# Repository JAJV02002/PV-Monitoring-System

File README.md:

# ☀️ PV Monitoring System

A photovoltaic monitoring project combining an ESP32 measurement unit, a PHP/MySQL web application, PCB designs and a printable enclosure. Developed for a bachelor’s thesis, the repository brings together the hardware and software resources for studying and recreating the system.

## 🌟 Features

- **Electrical measurements:** RMS voltage, RMS current, apparent power and an accumulated energy estimate.
- **Wi-Fi telemetry:** ESP32 measurements sent to the web application using HTTPS form requests.
- **Web dashboard:** Spanish and English interfaces with charts and historical readings.
- **Device management:** Devices grouped into matrices and measurement points.
- **Hardware resources:** KiCad schematic, board layout, required custom libraries, manufacturing outputs and a PCB assembly model.
- **Printable enclosure:** Separate STL files for the base and lid.

## 📁 Repository Structure

```text
PV-Monitoring-System/
├── hardware/
│   ├── bom/
│   │   └── EMON_BOM.xlsx
│   ├── cad/
│   │   ├── enclosure-base.stl
│   │   └── enclosure-lid.stl
│   └── pcb/
│       ├── kicad/
│       │   ├── monitoring-board.kicad_pro
│       │   ├── monitoring-board.kicad_sch
│       │   └── monitoring-board.kicad_pcb
│       ├── gerber/pcb-manufacturing.zip
│       └── 3d/pcb-assembly.zip
├── software/
│   ├── firmware/
│   │   ├── src/main.cpp
│   │   ├── include/secrets.example.h
│   │   └── platformio.ini
│   └── webapp/
│       ├── app/
│       ├── resources/
│       ├── index.php
│       └── .env.example
└── docs/
    └── architecture.md
```

Each component directory includes its own README with configuration and usage instructions.

## 🚀 Quick Start

### 1. Prepare the Hardware

1. Review the [Excel bill of materials](hardware/bom/EMON_BOM.xlsx).
2. Open the [KiCad project](hardware/pcb/kicad/README.md) and inspect the circuit and board layout.
3. Review the [manufacturing files](hardware/pcb/gerber/README.md) before ordering a PCB.
4. Inspect and print the [enclosure base and lid](hardware/cad/README.md), checking scale and fit against the board.

### 2. Configure the Web Application

Set up Apache, PHP with `mysqli`, and MySQL. Follow the [web application guide](software/webapp/README.md) to configure the document root, HTTPS and database connection.

```sh
cd software/webapp
cp .env.example .env
```

Enter the database credentials and a random hexadecimal device key in `.env`. A compatible database schema is required; the standalone schema is not yet published. See [database requirements](software/webapp/database/README.md).

### 3. Configure and Upload the Firmware

```sh
cd software/firmware
cp include/secrets.example.h include/secrets.h
```

Set the Wi-Fi credentials, HTTPS endpoint and matching device key in `secrets.h`, then build and upload:

```sh
pio run
pio run --target upload
pio device monitor
```

### 4. Connect the Measurement Point

Register the device with the web application, associate it with a measurement point, and confirm that readings appear in the database and dashboard. Check calibration against a suitable reference instrument.

## 📊 System Architecture

```text
Voltage and current signals
            │
            ▼
      ESP32 + sensors
  Sampling · RMS · Calibration
            │
            │ Wi-Fi / HTTPS form POST
            ▼
      PHP web application
    Controllers · Models · Views
            │
            ├── MySQL measurement storage
            │
            ▼
       Web dashboard
   Live views · History · Charts
```

## 🔧 Hardware

The Excel BOM contains core components and a high-precision sensing configuration, including the ESP32-DEVKITC-32E, HCPL-7800A-300E, OP177GSZ and HXS20-NP. Use the workbook as the component list and check compatibility with the intended PCB revision before assembly.

The manufacturing job describes a **two-layer, 1.6 mm board**, approximately **100.4 × 70.4 mm**. The enclosure is available as STL meshes, and the PCB assembly is available as a STEP model.

## 💻 Software Stack

| Component | Technology |
| --- | --- |
| Firmware | C++ / Arduino framework / PlatformIO |
| Microcontroller target | ESP32 development board (`esp32dev`) |
| Backend | PHP with an MVC-style structure |
| Database | MySQL through `mysqli` |
| Web server | Apache |
| Frontend | PHP views, HTML, CSS and JavaScript |
| Interface libraries | Bootstrap, Chart.js, jQuery and Popper |
| Telemetry | HTTPS with URL-encoded form fields |

## 📈 Measurement Details

- **ADC inputs:** GPIO 34 for voltage and GPIO 35 for current.
- **Sampling:** 12-bit resolution, 1,000 samples per block.
- **Averaging:** Voltage and current averaged over five blocks.
- **Power:** Apparent power calculated as `Vrms × Irms`.
- **Energy:** Time-integrated estimate assuming unity power factor; resets at restart.

The offset filter removes the DC component. Calibration and supported electrical ranges must be verified for the measurement hardware. See the [firmware guide](software/firmware/README.md) for timing and power-averaging details.

## 📖 Documentation

- [Hardware guide](hardware/README.md)
- [Bill of materials](hardware/bom/README.md)
- [Firmware setup](software/firmware/README.md)
- [Web application setup](software/webapp/README.md)
- [Database requirements](software/webapp/database/README.md)
- [Architecture and telemetry](docs/architecture.md)

## 📝 License
This project is licensed under the Creative Commons Attribution 4.0 License - see the [LICENSE](LICENSE.txt) file for details.

The web application is distributed under its existing [GNU GPL version 3 license](software/webapp/LICENSE). Third-party libraries retain their own notices. Separate licensing terms for the hardware, firmware and documentation are not yet specified.

## 🤝 Contributing

Improvements to documentation, reproducibility, hardware integration and software testing are welcome. Use repository issues to describe a problem or propose a change, and include the board revision and relevant configuration when reporting results.

## 🎓 Educational Use

The project supports study of embedded acquisition, electrical measurement, wireless telemetry and web-based monitoring in renewable-energy research.

## 🙏 Acknowledgments

- ESP32 and Arduino communities
- KiCad development community
- Bootstrap, Chart.js and other third-party library contributors

---

**Made with ❤️ for renewable energy monitoring**

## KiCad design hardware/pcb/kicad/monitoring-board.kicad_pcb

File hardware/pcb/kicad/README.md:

# 🛠️ KiCad PCB Design

Editable schematic, board layout and project-local component libraries for the monitoring unit.

## 📁 Project Files

- [monitoring-board.kicad_pro](monitoring-board.kicad_pro): project settings.
- [monitoring-board.kicad_sch](monitoring-board.kicad_sch): circuit schematic.
- [monitoring-board.kicad_pcb](monitoring-board.kicad_pcb): board layout.
- [fp-lib-table](fp-lib-table): project footprint-library registration.
- [sym-lib-table](sym-lib-table): project symbol-library registration.

## 🧩 Component Libraries

| Directory | Contents |
| --- | --- |
| [footprints.pretty](footprints.pretty) | 19 custom footprints, including the two logos placed on the board |
| [symbols](symbols) | 7 custom symbol libraries referenced by the schematic |
| [3dmodels](3dmodels) | 16 component STEP models referenced by the board |

The component selection follows the PCB component references and its design BOM, with the two board-logo footprints included because they are part of the layout. Unused parts, plugins, caches and backups are excluded. The purchasing BOM is [EMON_BOM.xlsx](../../bom/EMON_BOM.xlsx).

## 🚀 Getting Started

1. Install KiCad 8.0 or a compatible newer version with its standard symbol, footprint and 3D-model libraries.
2. Open `monitoring-board.kicad_pro` from this directory.
3. The project library tables resolve custom components through `${KIPRJMOD}`; no personal library-folder path is required.
4. Inspect the schematic, board and 3D view before editing or manufacturing.

Standard KiCad components remain linked to the installed libraries. The custom models in `3dmodels/` use project-relative paths. Keep this directory structure intact when copying the project.

## 🔗 Related Resources

- [Bill of materials](../../bom/README.md)
- [Manufacturing files](../gerber/README.md)
- [PCB assembly STEP model](../3d/README.md)
- [Enclosure meshes](../../cad/README.md)

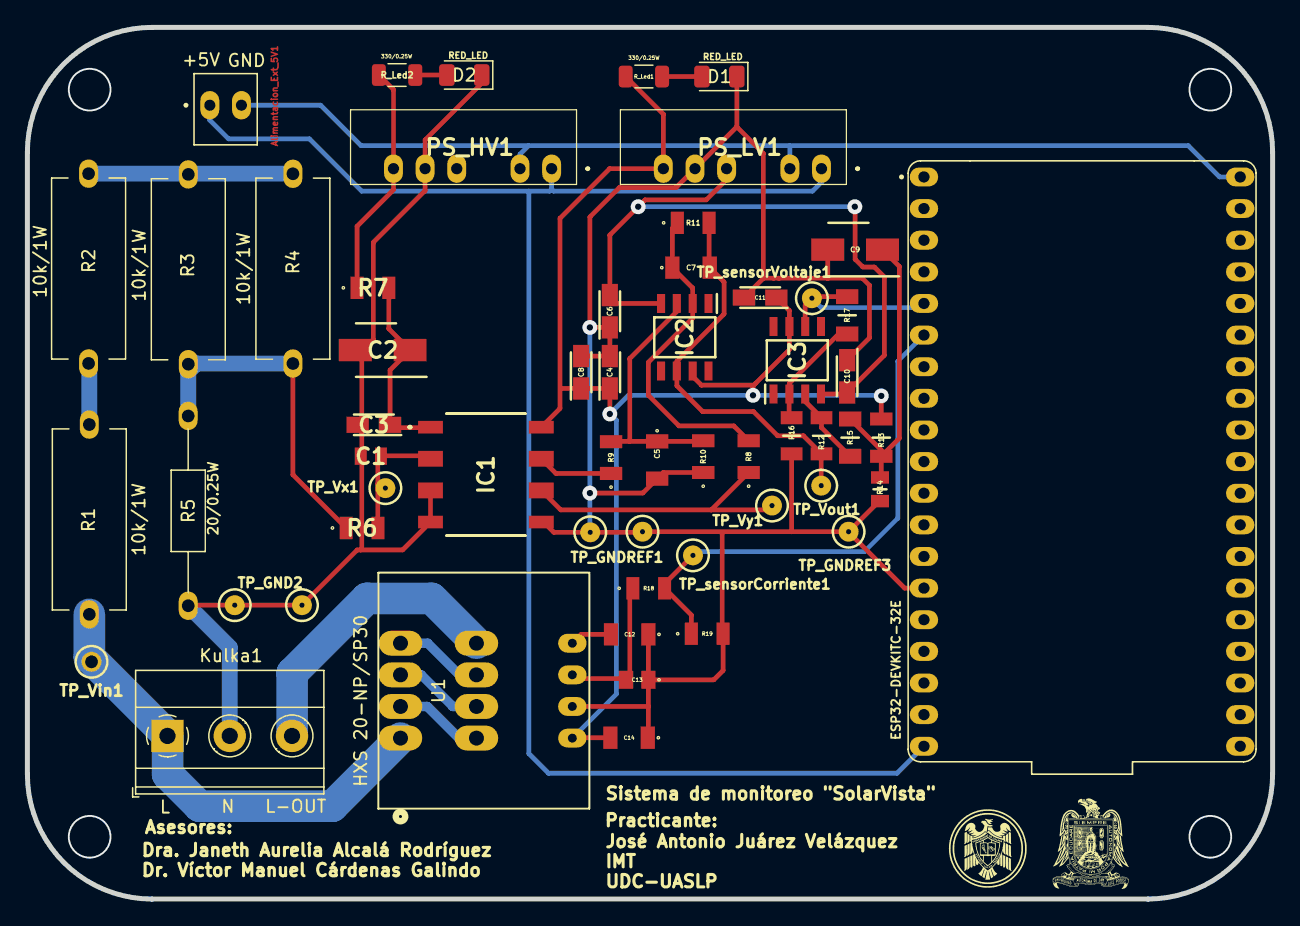
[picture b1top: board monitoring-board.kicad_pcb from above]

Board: 2 copper layers, 100.0 x 70.0 mm, 57 parts (0 on the bottom side), 31 nets.

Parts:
Alimentacion_Ext_5V1: 640456-2; header-640456-2
C1: 1000pF/Cer; capacitor-885012207060
C2, C9: 10uF/Elec; capacitor-EXV106M025A9BAA
C3, C4, C6, C8, C10, C11: 0.1uF/Tan; capacitor-TAJS104K020RNJ
C5, C7: 200pF/Cer; capacitor-C1206C201F4HACTU
C12, C14: 33nF/Cer; capacitor-C1206C201F4HACTU
C13: 3.3nF/Cer; capacitor-C0805C332F5GECAUTO7210
D1, D2: RED_LED; LED_1206_3216Metric
IC1: HCPL-7800A-300E
IC2, IC3: OP27GSZ
Kulka1: Screw_Terminal_01x03; TerminalBlock_Phoenix_MKDS-1,5-3_1x03_P5.00mm_Horizontal
PS_HV1: RB-0505D
PS_LV1: RB-0505D
R1, R2, R3, R4: 10k/1W; R_Axial_DIN0614_L14.3mm_D5.7mm_P15.24mm_Horizontal
R5: 20/0.25W; R_Axial_DIN0207_L6.3mm_D2.5mm_P15.24mm_Horizontal
R6, R19: 1k/0.25W; resistor-RCC12061R00FKEA
R7: 1/0.25W; resistor-RCC12061R00FKEA
R8, R9: 39k/0.25W; resistor-RCC12061R00FKEA
R10, R11: 22k/0.25W; resistor-RCC12061R00FKEA
R12, R16: 82k/0.25W; resistor-CRGH1206J82K
R13: 10k/0.25W; resistor-CRCW120610K0FKEAC
R14: 3.3k/0.25W; resistor-CR0805-FX-3301ELF
R15, R17: 100k/0.25W; resistor-CR1206-FX-1003ELF
R18: 1.2k/0.25W; resistor-RCC12061R00FKEA
R_Led1, R_Led2: 330/0.25W; R_1206_3216Metric
TP_GND1, TP_GND2: 5001; test-point-5001
TP_GNDREF1, TP_GNDREF2, TP_GNDREF3: 5001; test-point-5001
TP_Vin1: 5001; test-point-5001
TP_Vout1: 5001; test-point-5001
TP_Vx1: 5001; test-point-5001
TP_Vy1: 5001; test-point-5001
TP_sensorCorriente1: 5001; test-point-5001
TP_sensorVoltaje1: 5001; test-point-5001
U1: HXS 20-NP/SP30; HXS20-NP-SP30
U2: ESP32-DEVKITC-32E

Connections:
+5V_ESP: Alimentacion_Ext_5V1.1, PS_HV1.1 (+VIN), PS_LV1.1 (+VIN), U2.J2_19 (EXT_5V)
/currentSensor_Signal: R18.2, R19.1, TP_sensorCorriente1.1, U2.J2_6 (IO35)
/voltageSensor_Signal: IC3.6 (OUT), R17.2, TP_sensorVoltaje1.1, U2.J2_5 (IO34)
GNDREF: C4.2, C5.2, C6.1, C8.2, C9.2, C10.1, C11.2, C12.1, C13.1, C14.1, D1.1 (K), IC1.5 (GND2), PS_LV1.5 (COM), R10.1, R14.2, R16.1, R19.2, TP_GNDREF1.1, TP_GNDREF2.1, TP_GNDREF3.1, U1.10 (GND), U2.J2_14 (GND_J2_14)
GND_ESP: Alimentacion_Ext_5V1.2, PS_HV1.2 (-VIN), PS_LV1.2 (-VIN), U2.J3_1 (GND_J3_1)
Linea: Kulka1.1, R1.1, TP_Vin1.1, U1.1 (IN)
Linea_out: Kulka1.3, U1.8 (OUT)
unnamed: C9.1, R13.2, R14.1, R15.1
unnamed: C13.2, R18.1, U1.11 (OUT)
unnamed: D1.2 (A), R_Led1.1
unnamed: D2.2 (A), R_Led2.1
unnamed: C2.1, C3.1, IC1.1 (VDD1), R7.2
unnamed: C1.1, IC1.2 (VIN+), R6.2, TP_Vx1.1
unnamed: IC1.7 (VOUT+), R9.1
unnamed: IC1.6 (VOUT-), R8.1, TP_Vy1.1
unnamed: C5.1, IC2.3 (+IN), R9.2, R10.2
unnamed: C7.1, IC2.2 (-IN), R8.2, R11.1
unnamed: C7.2, IC2.6 (OUT), R11.2, R12.1, TP_Vout1.1
unnamed: IC3.3 (+IN), R12.2, R15.2
unnamed: IC3.2 (-IN), R16.2, R17.1
unnamed: R1.2, R2.1
unnamed: R2.2, R3.1, R4.1
unnamed: R3.2, R4.2, R5.1, R6.1
unnamed: U1.2 (OUT), U1.3 (IN)
unnamed: U1.4 (OUT), U1.5 (IN)
unnamed: U1.6 (OUT), U1.7 (IN)
unnamed: C12.2, U1.12 (REF)
Neutro: C1.2, C2.2, C3.2, D2.1 (K), IC1.3 (VIN-), IC1.4 (GND1), Kulka1.2, PS_HV1.5 (COM), R5.2, TP_GND1.1, TP_GND2.1
VDD1: PS_HV1.6 (+VOUT), R7.1, R_Led2.2
VDD2: C4.1, C8.1, C11.1, C14.2, IC1.8 (VDD2), IC2.7 (V+), IC3.7 (V+), PS_LV1.6 (+VOUT), R13.1, R_Led1.2, U1.9 (VC)
VEE: C6.2, C10.2, IC2.4 (V-), IC3.4 (V-), PS_LV1.4 (-VOUT)

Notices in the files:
README.md:
https://img.shields.io/badge/web%20app%20license-GPL--3.0-lightblue
